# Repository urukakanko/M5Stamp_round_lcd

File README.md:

# M5Stampラウンド液晶モジュール

M5Stampを使用して1.28インチ240ｘ240ドットの円形液晶を駆動する基板モジュールです。

円形液晶の裏にM5Stampを配置することで、とても小さくスリムな形状になりました。

円形液晶にはGC9A01というコントローラーが使用されていますが、対応したグラフィックライブラリが数種類公開されています。

本モジュールは「グラフィックライブラリの使い方を理解して液晶モジュールを駆動出来る人」をターゲットにしております。

# <span style="color: red;">注意！！（必ずお読み下さい）</span>

本品は基本的な電子回路の仕組みを理解した方を対象とした、電子部品がむき出しの半完成キットです。
電子部品は電源電圧や極性を間違えたり、部品を破損させたり部品端子をショートさせた場合、発熱・発煙・発火に至る場合もあります。
間違った使い方をすると危険である事を理解された方のみご使用ください。
趣味の電子工作向けに製作しておりますので、製品への組込みや日常生活へ組込んでのご使用はお控え下さい。

# 形状および回路図

以下に外形イメージを示します

以下に回路図を示します　現在最新は基板Ver1.2です

　基板Ver1.0の回路図などはこちら⇒
https://github.com/urukakanko/M5Stamp_round_lcd/tree/main/Ver1.0

　基板Ver1.1の回路図などはこちら⇒
https://github.com/urukakanko/M5Stamp_round_lcd/tree/main/Ver1.1

# ピンアサイン

M5Stamp とLCDの制御信号とのピン接続は以下となります。

- SCLK:G4

- MOSI:G6

- DC:G1

- CS:G7

- RST:G0

- バックライト:G10　バックライトLEDのPIN設定は必ず行ってください。ハイインピーダンスとなった場合バックライトが不安定になります。

また、I2C接続などを想定した外部接続端子があります

注意：リード線をハンダ付けするパットとして使用します　コネクタやピンヘッダは挿せません。　基板Ver1.0ではスルーホールになっていますが無理やり挿すとピン先がLCDにぶつかって破損したりショートする恐れがあります。
また、6PINおよび7PINはセンサーなど小型周辺モジュールを駆動するための電源出力端子です。本モジュールを駆動するための電源入力としては設計しておりません。

- 1PIN : GND

- 2PIN : G20

- 3PIN : G21

- 4PIN : G8 (I2C SDAを想定)

- 5PIN : G9 (I2C SCLを想定)

- 6PIN : 5V

- 7PIN : 3.3V(基板Ver1.0にはありません　基板Ver1.1より対応) 

「M5Stamp C3U」　および　「 M5Stamp C3」　両方が使用出来る様にG3端子は未接続にしています

# 使用するツールやライブラリ

M5StampのArduino IDEへのインストールは、以下サイトを参考下さい。

https://docs.m5stack.com/en/quick_start/m5core/arduino

グラフィックライブラリについてはlovyanさまのLovyanGFXにて動作確認をしています。

https://github.com/lovyan03/LovyanGFX

他、GC9A01に対応したライブラリが使用可能と考えています。

# そーたメイさま「つくるっち」に対応して頂きました

http://sohta02.web.fc2.com/familyday.html

事前に以下ツールでM5Stampラウンド液晶モジュールにファームウェアを書込んでください

https://sohta02.sakura.ne.jp/release/burnESP.20220930.zip

Chromeブラウザで以下つくるっち画面を開き「拡張機能を追加」から「M5Series」を追加してください

https://sohta02.sakura.ne.jp/tukurutch/

サンプルプログラムは以下です

https://github.com/urukakanko/M5Stamp_round_lcd/blob/main/M5Stamp%E3%82%B5%E3%83%B3%E3%83%97%E3%83%AB_%E3%83%8F%E3%83%83%E3%83%94%E3%83%BC%E3%83%8F%E3%83%AD%E3%82%A6%E3%82%A3%E3%83%B3.sb3

USB接続で以下の様に動かす事ができます

もちろんWiFiでの動作も可能です。詳細設定についてはそーたメイさまのサイトを参考にしてください

説明内のファームウェア書き込み操作は不要です【ファームウェア書き込み： マイコンを選択して [書き込み] をクリック】

http://sohta02.web.fc2.com/familyday_app3.html#setup_esp32

# LCD表示動画

https://youtu.be/kj006jx1wdU

# 製作過程動画

https://youtu.be/ezlkv9BLLXo

# 使用例

スマートウォッチはもちろん、アイコン表示でカードフォルダー代わり

ロボットに顔写真を表示すると、とても味のある雰囲気に・・・

AMG8833と組合わせると温度虫眼鏡も作れます　動画はこちら
https://youtu.be/yjvwYW8tv_Q

AMG8833サーマルカメラの作り方をまとめました　とても便利ですので興味がある方はご覧ください

https://github.com/urukakanko/M5Stamp_round_lcd/tree/main/thermal_cam_demo

カラフルな液晶バッジ

# スイッチサイエンスマーケットプレイスで販売しています
M5Stamp実装版
https://www.switch-science.com/catalog/8098/

M5Stamp未実装版
https://www.switch-science.com/catalog/8099/

# 製作者

ウルカテクノロジー
Hiroyuki Sunagawa

https://www.facebook.com/URUKA-Technologies-105478404379918

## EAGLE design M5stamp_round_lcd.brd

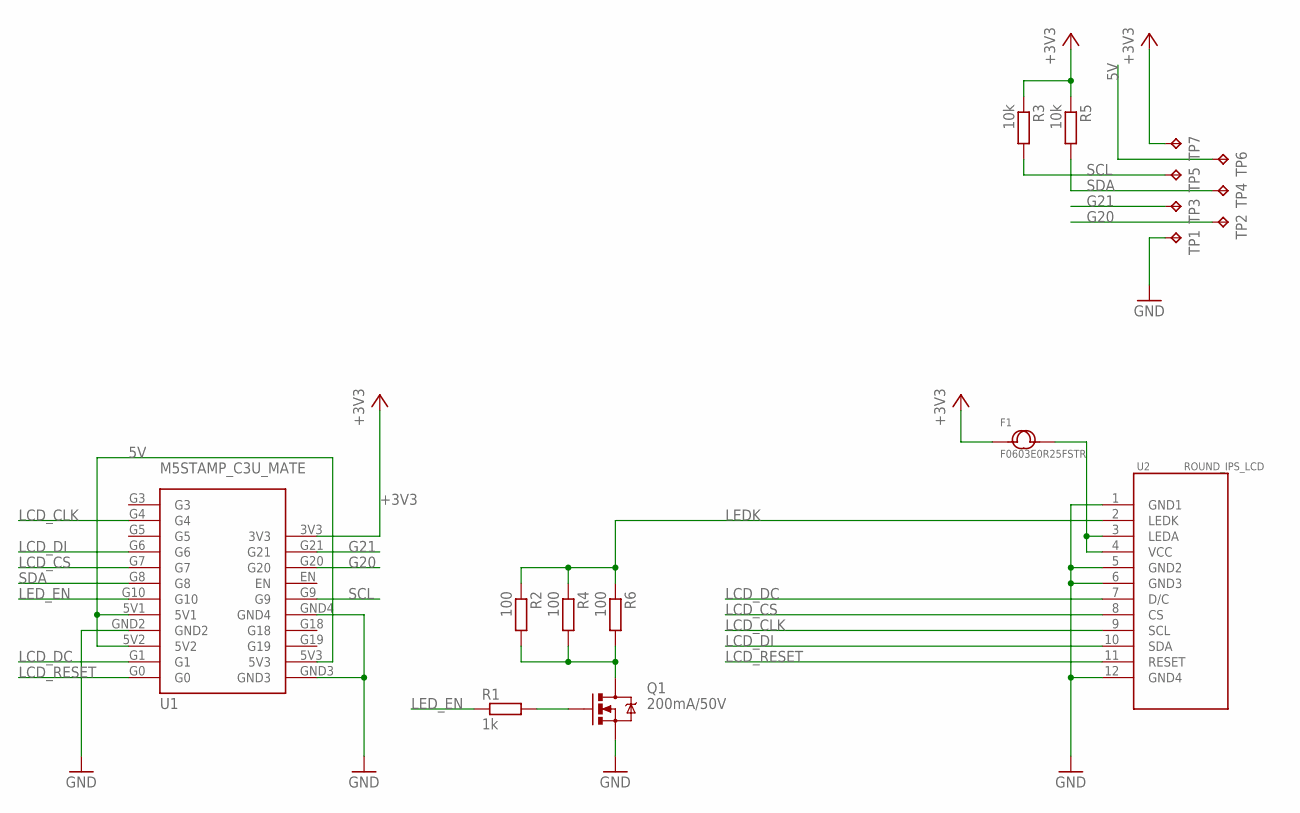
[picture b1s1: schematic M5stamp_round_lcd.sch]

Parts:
F1: F0603E0R25FSTR; C0603
Q1: 200mA/50V; SOT23-3
R1: 1k; R0603
R2, R4, R6: 100; R0603
R3, R5: 10k; R0603
TP1, TP2, TP3, TP4, TP5, TP6, TP7: TPTP18R; TP18R
U1: M5STAMP_C3U_MATE; M5STAMPC3UMATE
U2: ROUND_IPS_LCD

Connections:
5V: TP6.TP, U1.5V1, U1.5V2, U1.5V3
+3V3: F1.1, R3.1, R5.1, TP7.TP, U1.3V3
G20: TP2.TP, U1.G20
G21: TP3.TP, U1.G21
GND: Q1.2 (S), TP1.TP, U1.GND2, U1.GND3, U1.GND4, U2.1 (GND1), U2.5 (GND2), U2.6 (GND3), U2.12 (GND4)
LCD_CLK: U1.G4, U2.9 (SCL)
LCD_CS: U1.G7, U2.8 (CS)
LCD_DC: U1.G1, U2.7 (D/C)
LCD_DI: U1.G6, U2.10 (SDA)
LCD_RESET: U1.G0, U2.11 (RESET)
LEDK: R2.1, R4.1, R6.1, U2.2 (LEDK)
LED_EN: R1.1, U1.G10
unnamed: Q1.3 (D), R2.2, R4.2, R6.2
unnamed: Q1.1 (G), R1.2
unnamed: F1.2, U2.3 (LEDA), U2.4 (VCC)
SCL: R3.2, TP5.TP, U1.G9
SDA: R5.2, TP4.TP, U1.G8

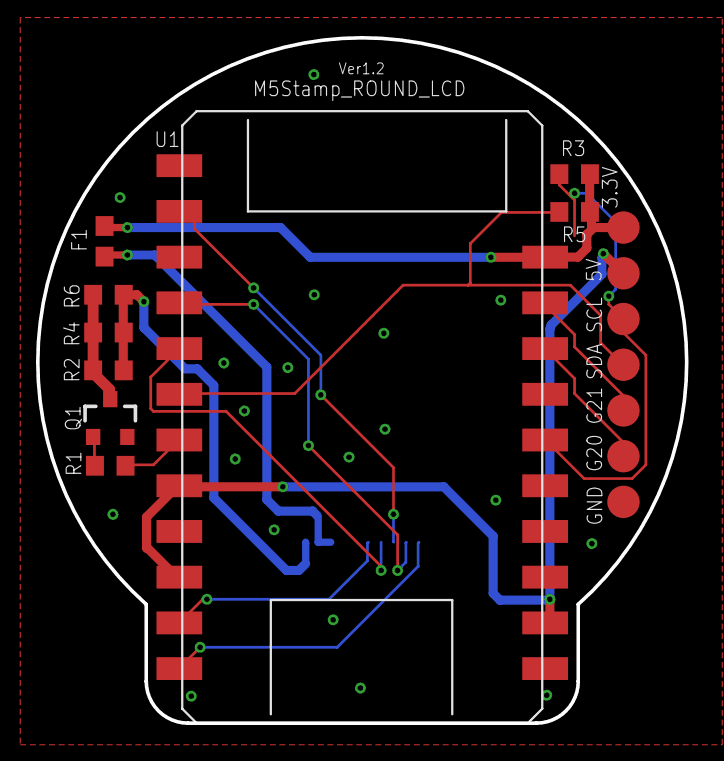
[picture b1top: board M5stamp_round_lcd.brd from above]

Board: 2 copper layers, 36.0 x 38.1 mm, 17 parts (1 on the bottom side), 17 nets.

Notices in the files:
parts and their libraries:
SparkFun-Aesthetics: Licensing: Creative Commons ShareAlike 4.0 International - https://creativecommons.org/licenses/by-sa/4.0
